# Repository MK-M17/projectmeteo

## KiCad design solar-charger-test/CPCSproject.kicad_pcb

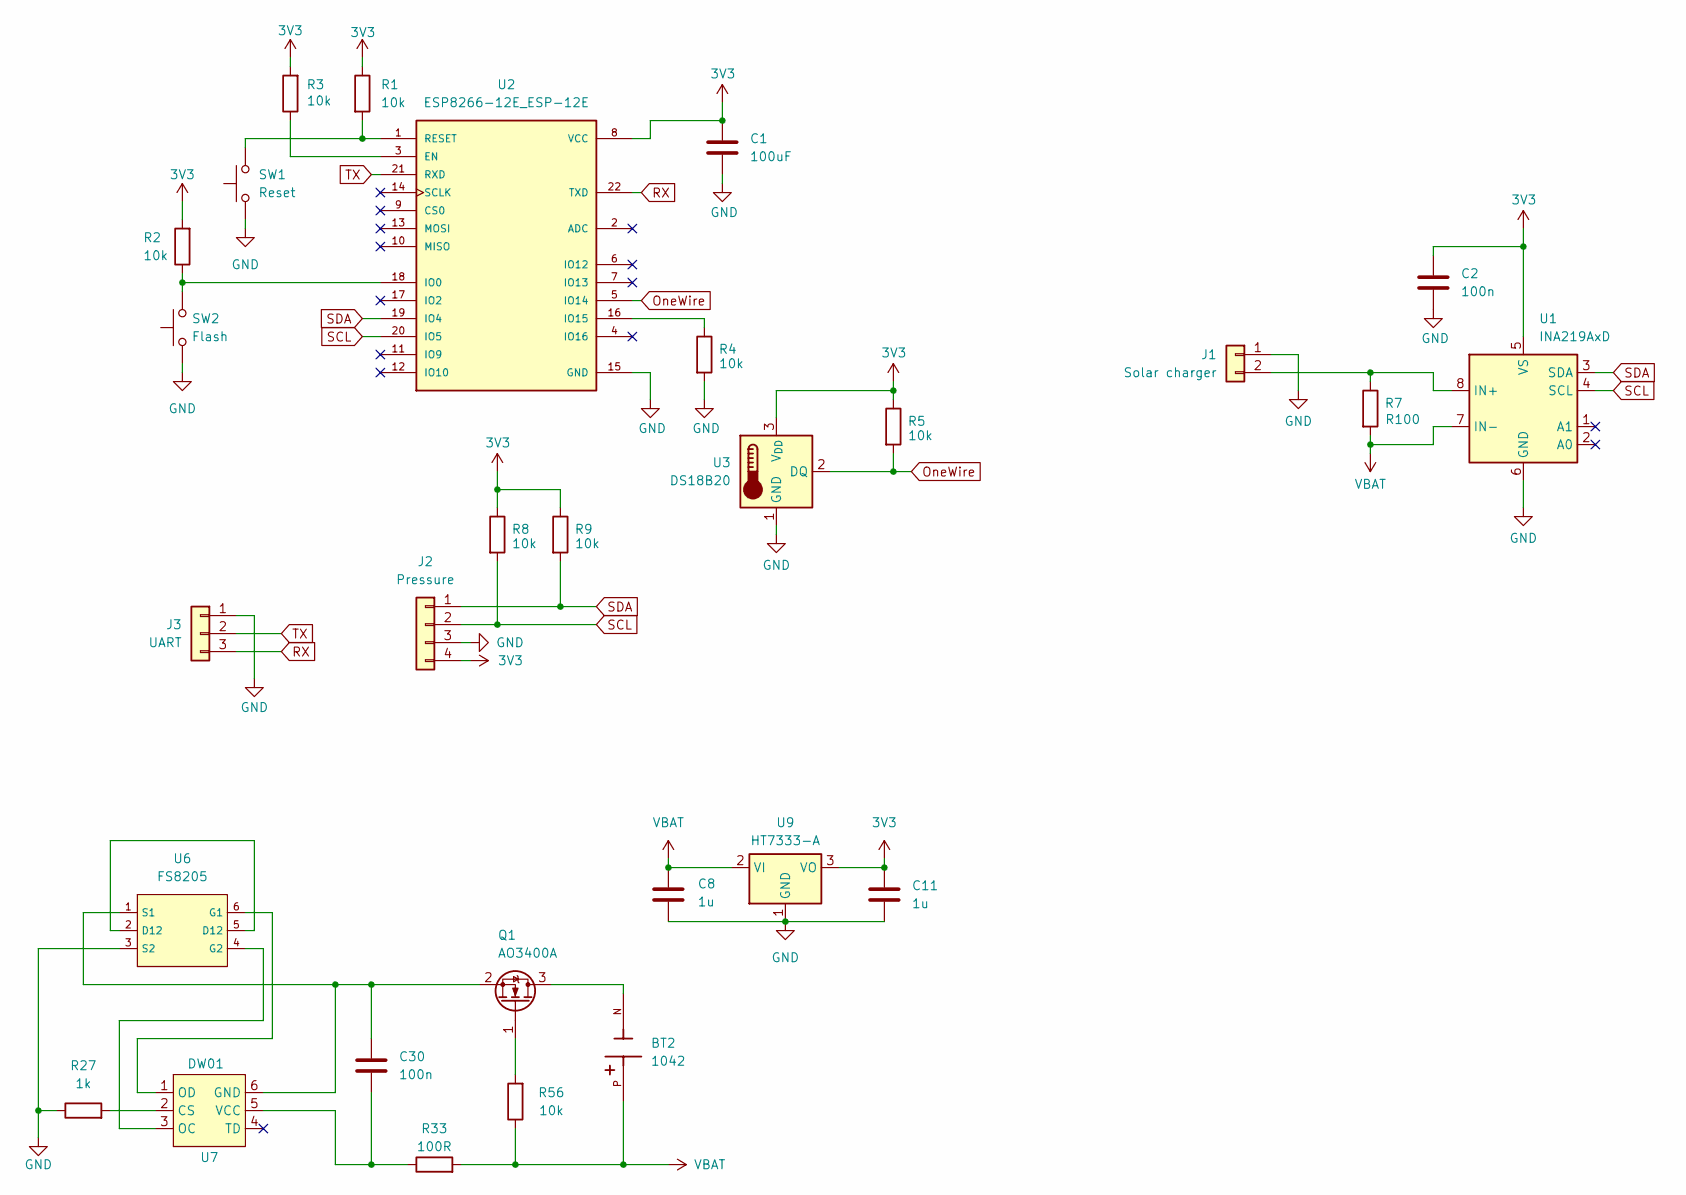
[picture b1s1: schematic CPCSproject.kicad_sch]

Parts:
BT2: 1042; BAT_1042; PARTREV E
C1: 100uF; C_1206_3216Metric_Pad1.33x1.80mm_HandSolder
C2, C30: 100n; C_0805_2012Metric_Pad1.18x1.45mm_HandSolder
C8, C11: 1u; C_0805_2012Metric_Pad1.18x1.45mm_HandSolder
J1: Solar charger; JST_PH_S2B-PH-SM4-TB_1x02-1MP_P2.00mm_Horizontal
J2: Pressure; PinSocket_1x04_P2.54mm_Horizontal
J3: UART; JST_PH_S3B-PH-SM4-TB_1x03-1MP_P2.00mm_Horizontal
Q1: AO3400A; SOT-23
R1, R2, R3, R4, R5, R8, R9, R56: 10k; R_0805_2012Metric_Pad1.20x1.40mm_HandSolder
R7: R100; R_2512_6332Metric_Pad1.40x3.35mm_HandSolder
R27: 1k; R_0805_2012Metric_Pad1.20x1.40mm_HandSolder
R33: 100R; R_0805_2012Metric_Pad1.20x1.40mm_HandSolder
SW1: Reset; SW_SPST_PTS645Sx43SMTR92
SW2: Flash; SW_SPST_PTS645Sx43SMTR92
U1: INA219AxD; SOIC-8_3.9x4.9mm_P1.27mm
U2: ESP8266-12E_ESP-12E; XCVR_ESP8266-12E_ESP-12E
U3: DS18B20; TO-92_Inline
U6: FS8205; SOT-23-6_Handsoldering
U7: DW01; SOT-23-6_Handsoldering
U9: HT7333-A; SOT-89-3

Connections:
3V3: C1.1, C2.1, C11.1, J2.4, R1.1, R2.2, R3.2, R5.1, R8.1, R9.1, U1.5 (VS), U2.8 (VCC), U3.3 (V_{DD}), U9.3 (VO)
GND: C1.2, C2.2, C8.2, C11.2, J1.1, J2.3, J3.1, R4.2, R27.1, SW1.1, SW2.2, U1.6 (GND), U2.15 (GND), U3.1 (GND), U6.3 (S2), U9.1 (GND)
unnamed: J1.2, R7.1, U1.8 (IN+)
unnamed: BT2.N, Q1.3 (D)
unnamed: Q1.1 (G), R56.2
unnamed: C30.1, Q1.2 (S), U6.1 (S1), U7.6 (GND)
unnamed: R3.1, U2.3 (EN)
unnamed: R2.1, SW2.1, U2.18 (IO0)
unnamed: R4.1, U2.16 (IO15)
unnamed: R1.2, SW1.2, U2.1 (RESET)
unnamed: U6.2 (D12), U6.5 (D12)
unnamed: U6.6 (G1), U7.1 (OD)
unnamed: U6.4 (G2), U7.3 (OC)
unnamed: R27.2, U7.2 (CS)
unnamed: C30.2, R33.1, U7.5 (VCC)
OneWire: R5.2, U2.5 (IO14), U3.2 (DQ)
RX: J3.3, U2.22 (TXD)
SCL: J2.2, R8.2, U1.4 (SCL), U2.20 (IO5)
SDA: J2.1, R9.2, U1.3 (SDA), U2.19 (IO4)
TX: J3.2, U2.21 (RXD)
VBAT: BT2.P, C8.1, R7.2, R33.2, R56.1, U1.7 (IN-), U9.2 (VI)

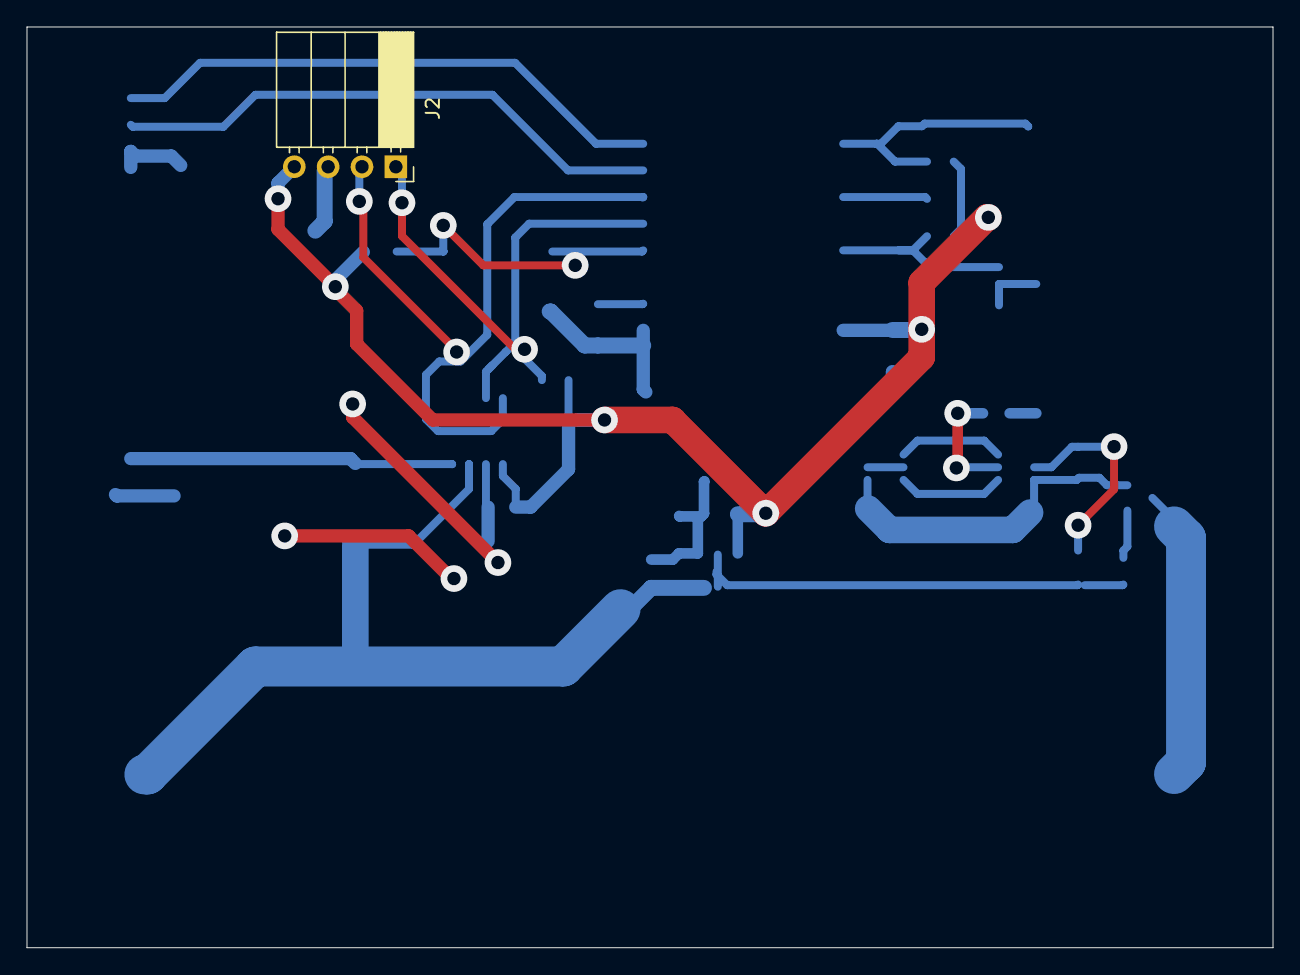
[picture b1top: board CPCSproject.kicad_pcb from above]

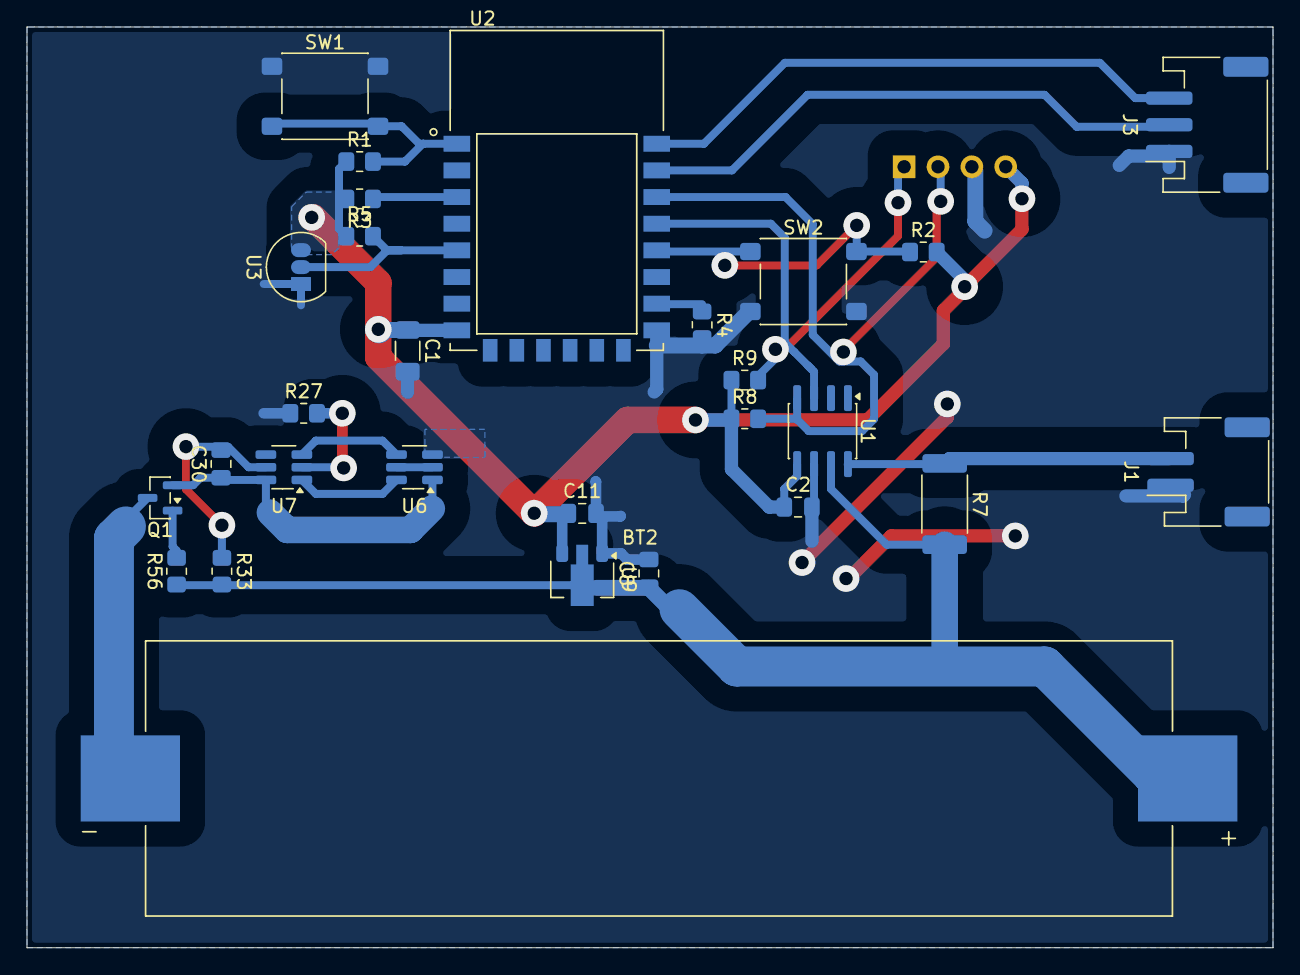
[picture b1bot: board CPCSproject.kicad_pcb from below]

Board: 2 copper layers, 93.5 x 69.1 mm, 29 parts (28 on the bottom side), 21 nets.
